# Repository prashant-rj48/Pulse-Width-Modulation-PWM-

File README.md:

# PWM-Based Power Control System Using IC 555 & KiCad PCB Design
Pulse Width Modulation (PWM)-based power control system using IC 555 timer, transistor switching, and duty-cycle modulation techniques.
The project demonstrates how PWM can efficiently control output power in real-world applications such as electric vehicle motor control, DC fan regulation, industrial actuators, and power electronics systems.

An LED load was used as a visual hardware indicator to demonstrate real-time PWM operation and switching behavior.

***

# Features
PWM signal generation using IC 555 timer.

Duty-cycle-based power control technique.

Potentiometer-controlled pulse width adjustment.

Efficient power regulation without varying supply voltage.

Complete schematic and PCB design using KiCad.

Hardware implementation on General Purpose PCB board.

Real-time PWM output visualization using LED load.

***

# PWM Concept
## IC 555
The IC 555 generates high-frequency ON/OFF pulses by charging and discharging a capacitor through diodes and a potentiometer.

Higher ON time → higher average output power
Lower ON time → lower average output power

The load receives varying average power depending on duty cycle.

##
## Duty Cycle

## Role of Potentiometer
The potentiometer changes the charging and discharging timing of the capacitor connected to the 555 timer.

This directly controls:- Pulse width, Duty cycle, Average output power

***

## Working Principle

    Power Supply
           │
           ▼
    555 Timer IC ───► PWM Signal Generation
           │
           ▼
    Potentiometer ───► Duty Cycle Control
           │
           ▼
     Transistor Switching Stage
           │
           ▼
      Output Load (LED Demonstration)

***

# PCB Design

## Schematic 

## PCB layout

## 3-D View

***

# Applications
Electric vehicle speed controllers

DC motor control systems

Industrial PWM drives

Robotics power control

Fan speed controllers

Smart lighting systems

Embedded electronics prototyping

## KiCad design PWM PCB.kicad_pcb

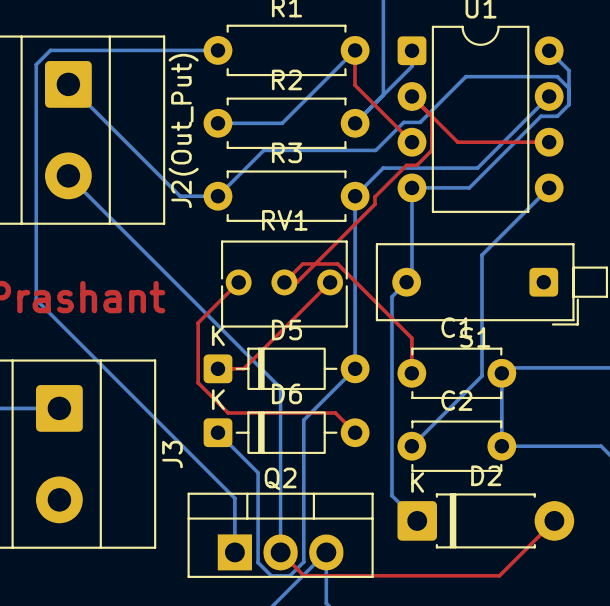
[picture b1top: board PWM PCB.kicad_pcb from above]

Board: 2 copper layers, 14 parts (0 on the bottom side), 10 nets.

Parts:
C1: 10nF; C_Disc_D4.7mm_W2.5mm_P5.00mm
C2: 0.1M; C_Disc_D4.7mm_W2.5mm_P5.00mm
D2: D; D_DO-41_SOD81_P7.62mm_Horizontal
D5, D6: 1N4148; D_DO-35_SOD27_P7.62mm_Horizontal
J2(Out_Put), J3: Screw_Terminal_01x02; TerminalBlock_Phoenix_MKDS-1,5-2-5.08_1x02_P5.08mm_Horizont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
Q2: IRLZ24; TO-220-3_Vertical
R1, R2, R3: 1K; R_Axial_DIN0207_L6.3mm_D2.5mm_P7.62mm_Horizontal
RV1: R_Potentiometer; Potentiometer_Bourns_3266Y_Vertical
S1: SWITCH; SW_DIP_SPSTx01_Piano_10.8x4.1mm_W7.62mm_P2.54mm
U1: LM555xN; DIP-8_W7.62mm

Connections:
Earth: C1.2, C2.2, J3.1, Q2.3 (S), R2.2, U1.1 (GND)
unnamed: D2.2 (A), J2(Out_Put).2, Q2.2 (D)
unnamed: D2.1 (K), J2(Out_Put).1, R3.1, S1.2 (N-), U1.4 (R), U1.8 (VCC)
unnamed: D5.2 (A), D6.1 (K), R3.2, U1.7 (DIS)
unnamed: D5.1 (K), RV1.1
unnamed: D6.2 (A), RV1.3
unnamed: Q2.1 (G), R1.1
unnamed: C2.1, U1.5 (CV)
unnamed: R1.2, R2.1, U1.3 (Q)
unnamed: C1.1, RV1.2, U1.2 (TR), U1.6 (THR)
